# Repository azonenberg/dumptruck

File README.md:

# dumptruck
FPGA based dumper for flashes and more

## Main PCB errata

Bugs in the v0.1 PCB

* 1.0V shunt resistor is missing a zone fill. Will monitor droop under load and see if we need to add top layer power path.
* U33 is way too close to J10. Seems to have fit OK, not touching for now, but tough to assemble.
* INIT_B and PROG_B on FPGA are 1.8V signals but we try to drive with 3.3 from supervisor! Rework: add pull to 1.8V on board, open drain in super firmware
* JTAG connector VCC is connected to 3.3V. We need to supply 1.8 here. Temporary workaround: six pin extension cable, pass through JTAG + GND and supply 1.8V to dongle externally. Long term fix: interposer board
* DONE on FPGA is 1.8V signal driving 3.3V input on supervisor, too low for Vih. Rework: add 1.8V gate drive NMOS to pull low when done, invert logic in firmware

TODO: add HF caps to VCAP on STM32

## Breakout board errata

* v0.1 of parallel-nor-csp56 and dip8-qspi had EEPROM at 0xa0 which conflicted with MAC address EEPROM. Future breakouts use 0xa2 to avoid conflict

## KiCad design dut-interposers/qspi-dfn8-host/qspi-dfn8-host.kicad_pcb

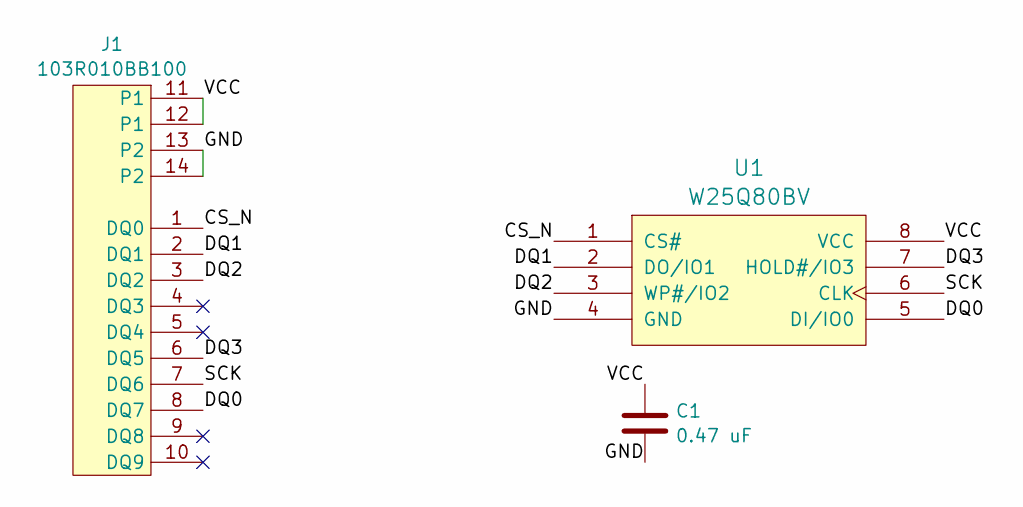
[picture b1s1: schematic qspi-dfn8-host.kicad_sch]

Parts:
C1: 0.47 uF; EIA_0402_CAP_NOSILK
J1: 103R010BB100; CONN_AMPHENOL_103R010BB100
U1: W25Q80BV; DFN_8_0.5MM_2x3MM_TALL

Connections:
/CS_N: J1.1 (DQ0), U1.1 (CS#)
/DQ0: J1.8 (DQ7), U1.5 (DI/IO0)
/DQ1: J1.2 (DQ1), U1.2 (DO/IO1)
/DQ2: J1.3 (DQ2), U1.3 (WP#/IO2)
/DQ3: J1.6 (DQ5), U1.7 (HOLD#/IO3)
/GND: C1.2, J1.13 (P2), J1.14 (P2), U1.4 (GND)
/SCK: J1.7 (DQ6), U1.6 (CLK)
/VCC: C1.1, J1.11 (P1), J1.12 (P1), U1.8 (VCC)

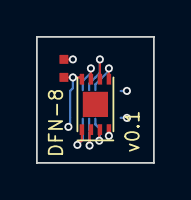
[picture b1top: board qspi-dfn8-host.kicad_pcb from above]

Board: 4 copper layers, 6.5 x 7.0 mm, 3 parts (1 on the bottom side), 8 nets.

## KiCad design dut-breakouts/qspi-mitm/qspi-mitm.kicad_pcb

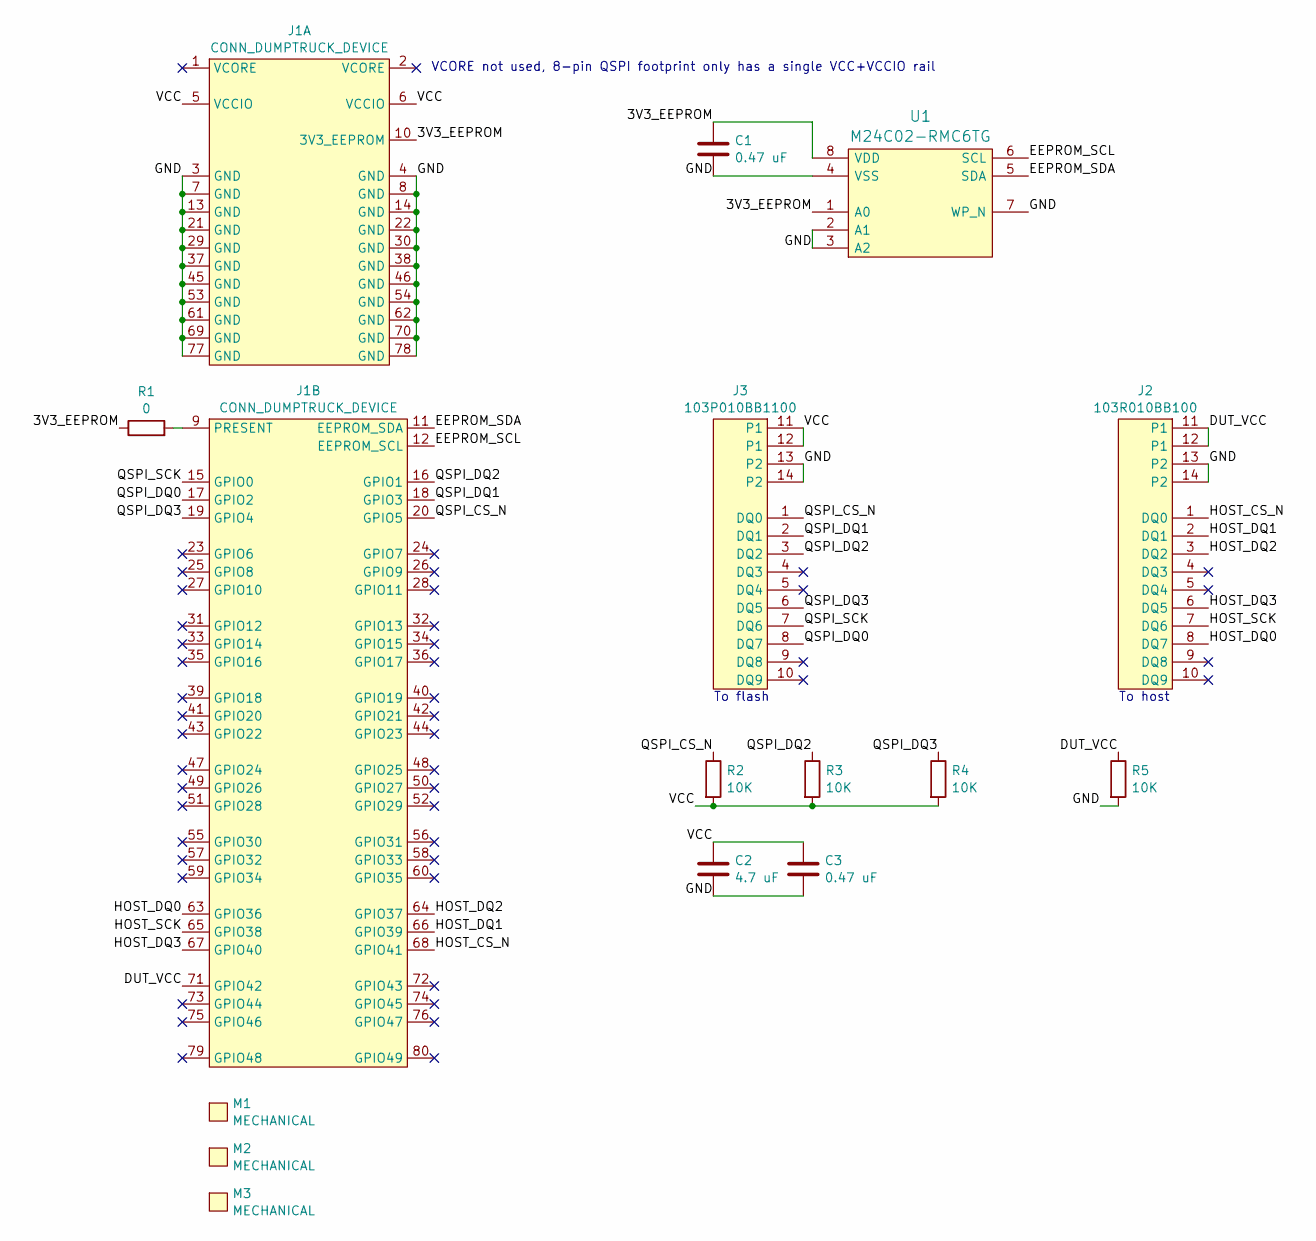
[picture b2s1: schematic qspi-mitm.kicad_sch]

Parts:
C1, C3: 0.47 uF; EIA_0402_CAP_NOSILK
C2: 4.7 uF; EIA_0603_CAP_NOSILK
J1: CONN_DUMPTRUCK_DEVICE; CONN_SAMTEC_BSE-040-01-L-D-A-TR
J2: 103R010BB100; CONN_AMPHENOL_103R010BB100
J3: 103P010BB1100; CONN_AMPHENOL_103P010BB100
M1: MECHANICAL; Logo_silk_ROHS_5x2.8mm
M2: MECHANICAL; Logo_silk_OSHW_6x6mm
M3: MECHANICAL; Logo_silk_WEEE_3.4x5mm
R1: 0; EIA_0402_RES_NOSILK
R2, R3, R4, R5: 10K; EIA_0402_RES_NOSILK
U1: M24C02-RMC6TG; DFN_8_0.5MM_2x3MM_TALL

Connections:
/3V3_EEPROM: C1.1, J1.10 (3V3_EEPROM), R1.1, U1.1 (A0), U1.8 (VDD)
/DUT_VCC: J1.71 (GPIO42), J2.11 (P1), J2.12 (P1), R5.1
/EEPROM_SCL: J1.12 (EEPROM_SCL), U1.6 (SCL)
/EEPROM_SDA: J1.11 (EEPROM_SDA), U1.5 (SDA)
/GND: C1.2, C2.2, C3.2, J1.3 (GND), J1.4 (GND), J1.7 (GND), J1.8 (GND), J1.13 (GND), J1.14 (GND), J1.21 (GND), J1.22 (GND), J1.29 (GND), J1.30 (GND), J1.37 (GND), J1.38 (GND), J1.45 (GND), J1.46 (GND), J1.53 (GND), J1.54 (GND), J1.61 (GND), J1.62 (GND), J1.69 (GND), J1.70 (GND), J1.77 (GND), J1.78 (GND), J2.13 (P2), J2.14 (P2), J3.13 (P2), J3.14 (P2), R5.2, U1.2 (A1), U1.3 (A2), U1.4 (VSS), U1.7 (WP_N)
/HOST_CS_N: J1.68 (GPIO41), J2.1 (DQ0)
/HOST_DQ0: J1.63 (GPIO36), J2.8 (DQ7)
/HOST_DQ1: J1.66 (GPIO39), J2.2 (DQ1)
/HOST_DQ2: J1.64 (GPIO37), J2.3 (DQ2)
/HOST_DQ3: J1.67 (GPIO40), J2.6 (DQ5)
/HOST_SCK: J1.65 (GPIO38), J2.7 (DQ6)
/QSPI_CS_N: J1.20 (GPIO5), J3.1 (DQ0), R2.1
/QSPI_DQ0: J1.17 (GPIO2), J3.8 (DQ7)
/QSPI_DQ1: J1.18 (GPIO3), J3.2 (DQ1)
/QSPI_DQ2: J1.16 (GPIO1), J3.3 (DQ2), R3.1
/QSPI_DQ3: J1.19 (GPIO4), J3.6 (DQ5), R4.1
/QSPI_SCK: J1.15 (GPIO0), J3.7 (DQ6)
/VCC: C2.1, C3.1, J1.5 (VCCIO), J1.6 (VCCIO), J3.11 (P1), J3.12 (P1), R2.2, R3.2, R4.2
unnamed: J1.9 (PRESENT), R1.2

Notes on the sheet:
To host
VCORE not used, 8-pin QSPI footprint only has a single VCC+VCCIO rail
To flash

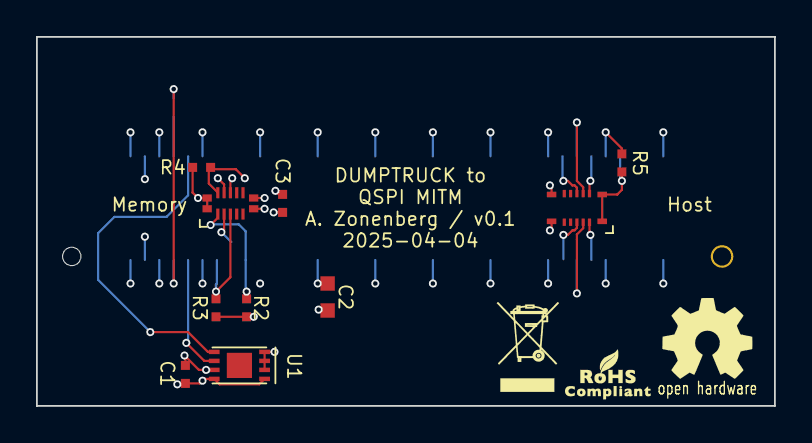
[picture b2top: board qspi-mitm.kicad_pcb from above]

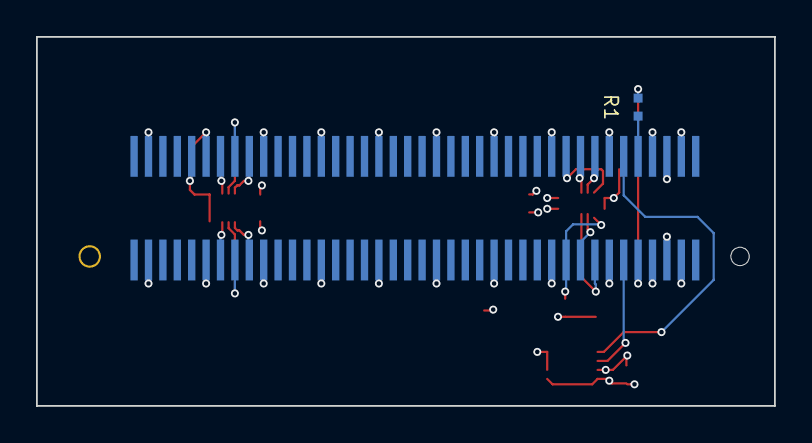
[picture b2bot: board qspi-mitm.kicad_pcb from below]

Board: 4 copper layers, 41.0 x 20.5 mm, 15 parts (2 on the bottom side), 19 nets.

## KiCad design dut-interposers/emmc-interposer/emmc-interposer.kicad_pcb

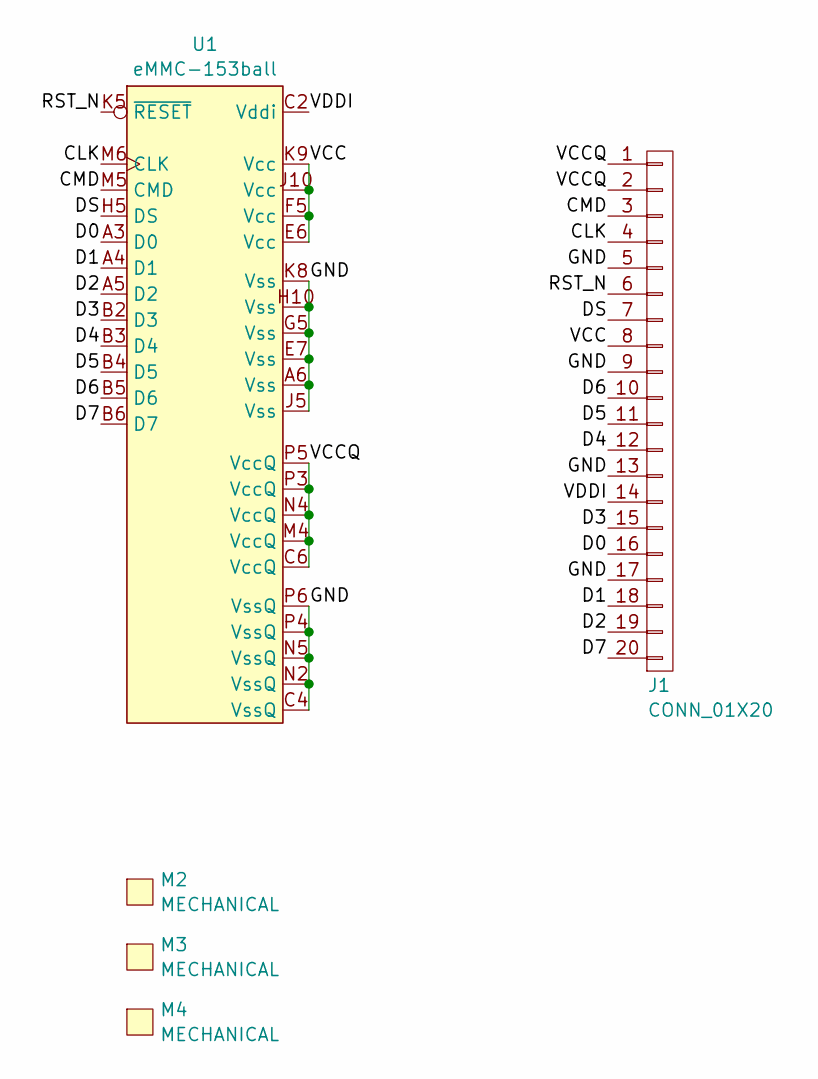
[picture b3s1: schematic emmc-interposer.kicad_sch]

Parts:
J1: CONN_01X20; CONN_FFC_0.5MM_3.5MM_1x20_2MM
M2: MECHANICAL; Logo_silk_OSHW_6x6mm
M3: MECHANICAL; Logo_silk_WEEE_3.4x5mm
M4: MECHANICAL; Logo_silk_ROHS_5x2.8mm
U1: eMMC-153ball; BGA_153_14x14_EMMC_BA_0.5MM_NCDEPOP_REVERSE

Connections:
/CLK: J1.4, U1.M6 (CLK)
/CMD: J1.3, U1.M5 (CMD)
/D0: J1.16, U1.A3 (D0)
/D1: J1.18, U1.A4 (D1)
/D2: J1.19, U1.A5 (D2)
/D3: J1.15, U1.B2 (D3)
/D4: J1.12, U1.B3 (D4)
/D5: J1.11, U1.B4 (D5)
/D6: J1.10, U1.B5 (D6)
/D7: J1.20, U1.B6 (D7)
/DS: J1.7, U1.H5 (DS)
/GND: J1.5, J1.9, J1.13, J1.17, U1.A6 (Vss), U1.C4 (VssQ), U1.E7 (Vss), U1.G5 (Vss), U1.H10 (Vss), U1.J5 (Vss), U1.K8 (Vss), U1.N2 (VssQ), U1.N5 (VssQ), U1.P4 (VssQ), U1.P6 (VssQ)
/RST_N: J1.6, U1.K5 (~RESET)
/VCC: J1.8, U1.E6 (Vcc), U1.F5 (Vcc), U1.J10 (Vcc), U1.K9 (Vcc)
/VCCQ: J1.1, J1.2, U1.C6 (VccQ), U1.M4 (VccQ), U1.N4 (VccQ), U1.P3 (VccQ), U1.P5 (VccQ)
/VDDI: J1.14, U1.C2 (Vddi)

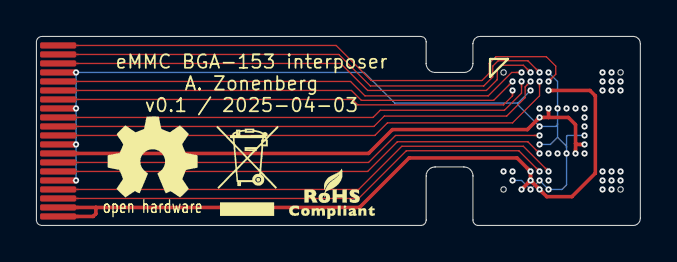
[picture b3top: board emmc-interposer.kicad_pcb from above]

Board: 2 copper layers, 33.5 x 10.5 mm, 5 parts (0 on the bottom side), 16 nets.

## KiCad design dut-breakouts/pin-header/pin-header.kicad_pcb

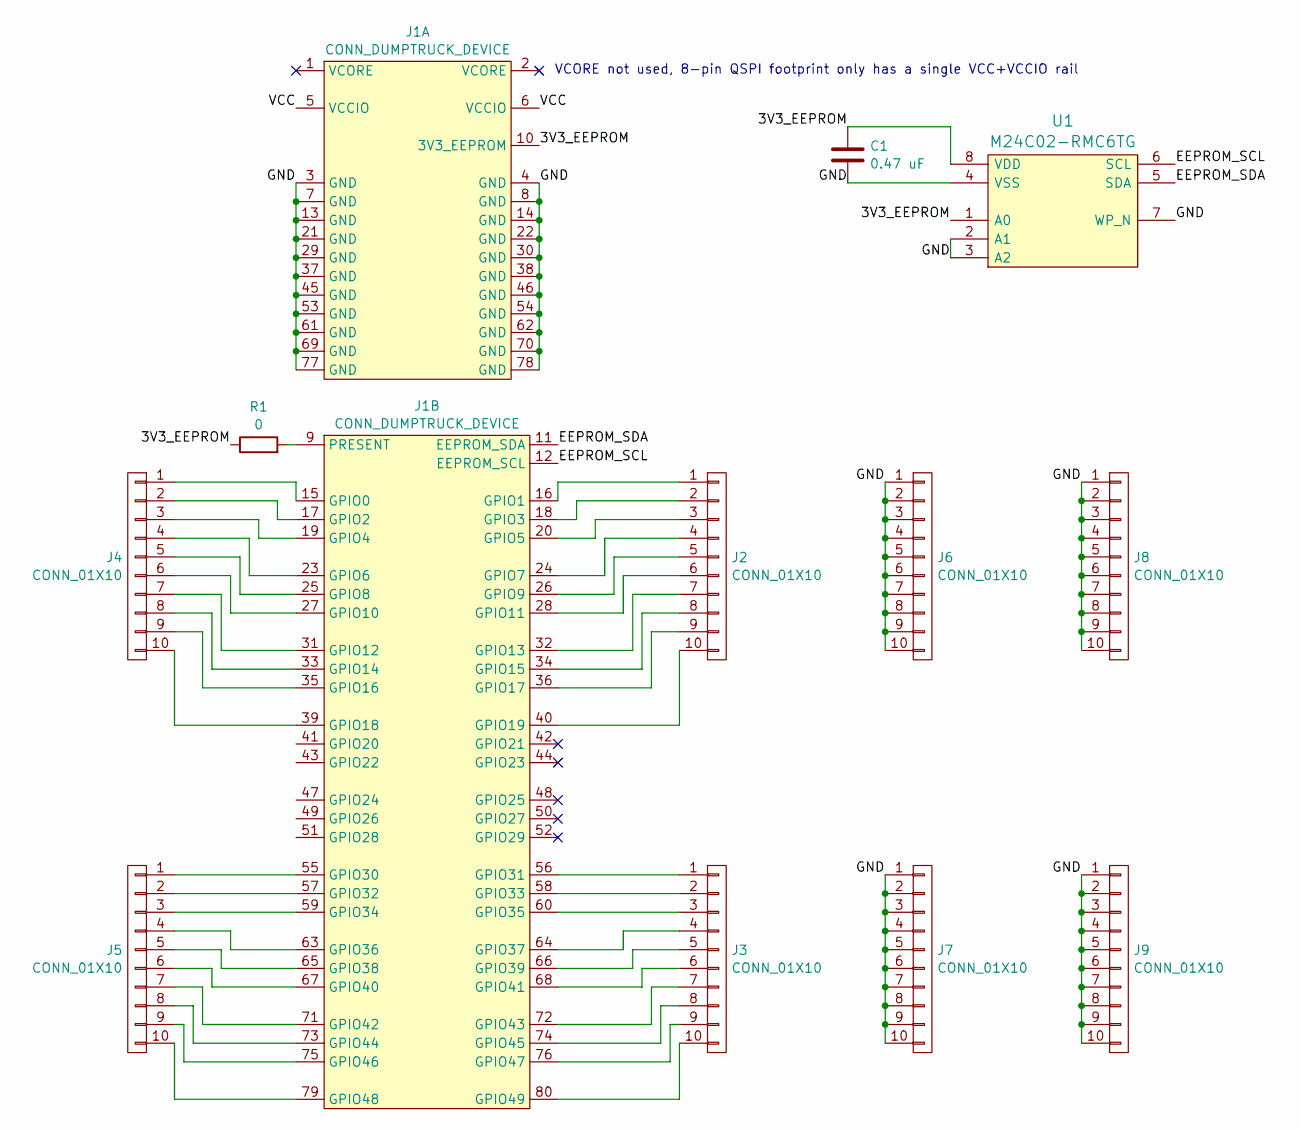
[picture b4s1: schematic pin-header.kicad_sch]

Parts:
C1: 0.47 uF; EIA_0402_CAP_NOSILK
J1: CONN_DUMPTRUCK_DEVICE; CONN_SAMTEC_BSE-040-01-L-D-A-TR
J2, J3, J4, J5, J6, J7, J8, J9: CONN_01X10; CONN_HEADER_2.54MM_1x10_REFLOW_NOSILK
R1: 0; EIA_0402_RES_NOSILK
U1: M24C02-RMC6TG; DFN_8_0.5MM_2x3MM_TALL

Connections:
/3V3_EEPROM: C1.1, J1.10 (3V3_EEPROM), R1.1, U1.1 (A0), U1.8 (VDD)
/EEPROM_SCL: J1.12 (EEPROM_SCL), U1.6 (SCL)
/EEPROM_SDA: J1.11 (EEPROM_SDA), U1.5 (SDA)
/GND: C1.2, J1.3 (GND), J1.4 (GND), J1.7 (GND), J1.8 (GND), J1.13 (GND), J1.14 (GND), J1.21 (GND), J1.22 (GND), J1.29 (GND), J1.30 (GND), J1.37 (GND), J1.38 (GND), J1.45 (GND), J1.46 (GND), J1.53 (GND), J1.54 (GND), J1.61 (GND), J1.62 (GND), J1.69 (GND), J1.70 (GND), J1.77 (GND), J1.78 (GND), J6.1, J6.2, J6.3, J6.4, J6.5, J6.6, J6.7, J6.8, J6.9, J6.10, J7.1, J7.2, J7.3, J7.4, J7.5, J7.6, J7.7, J7.8, J7.9, J7.10, J8.1, J8.2, J8.3, J8.4, J8.5, J8.6, J8.7, J8.8, J8.9, J8.10, J9.1, J9.2, J9.3, J9.4, J9.5, J9.6, J9.7, J9.8, J9.9, J9.10, U1.2 (A1), U1.3 (A2), U1.4 (VSS), U1.7 (WP_N)
/VCC: J1.5 (VCCIO), J1.6 (VCCIO)
unnamed: J1.15 (GPIO0), J4.1
unnamed: J1.16 (GPIO1), J2.1
unnamed: J1.17 (GPIO2), J4.2
unnamed: J1.18 (GPIO3), J2.2
unnamed: J1.19 (GPIO4), J4.3
unnamed: J1.20 (GPIO5), J2.3
unnamed: J1.23 (GPIO6), J4.4
unnamed: J1.24 (GPIO7), J2.4
unnamed: J1.25 (GPIO8), J4.5
unnamed: J1.26 (GPIO9), J2.5
unnamed: J1.27 (GPIO10), J4.6
unnamed: J1.28 (GPIO11), J2.6
unnamed: J1.31 (GPIO12), J4.7
unnamed: J1.32 (GPIO13), J2.7
unnamed: J1.33 (GPIO14), J4.8
unnamed: J1.34 (GPIO15), J2.8
unnamed: J1.35 (GPIO16), J4.9
unnamed: J1.36 (GPIO17), J2.9
unnamed: J1.39 (GPIO18), J4.10
unnamed: J1.40 (GPIO19), J2.10
unnamed: J1.55 (GPIO30), J5.1
unnamed: J1.56 (GPIO31), J3.1
unnamed: J1.57 (GPIO32), J5.2
unnamed: J1.58 (GPIO33), J3.2
unnamed: J1.59 (GPIO34), J5.3
unnamed: J1.60 (GPIO35), J3.3
unnamed: J1.63 (GPIO36), J5.4
unnamed: J1.64 (GPIO37), J3.4
unnamed: J1.65 (GPIO38), J5.5
unnamed: J1.66 (GPIO39), J3.5
unnamed: J1.67 (GPIO40), J5.6
unnamed: J1.68 (GPIO41), J3.6
unnamed: J1.71 (GPIO42), J5.7
unnamed: J1.72 (GPIO43), J3.7
unnamed: J1.73 (GPIO44), J5.8
unnamed: J1.74 (GPIO45), J3.8
unnamed: J1.75 (GPIO46), J5.9
unnamed: J1.76 (GPIO47), J3.9
unnamed: J1.79 (GPIO48), J5.10
unnamed: J1.80 (GPIO49), J3.10
unnamed: J1.9 (PRESENT), R1.2

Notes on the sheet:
VCORE not used, 8-pin QSPI footprint only has a single VCC+VCCIO rail

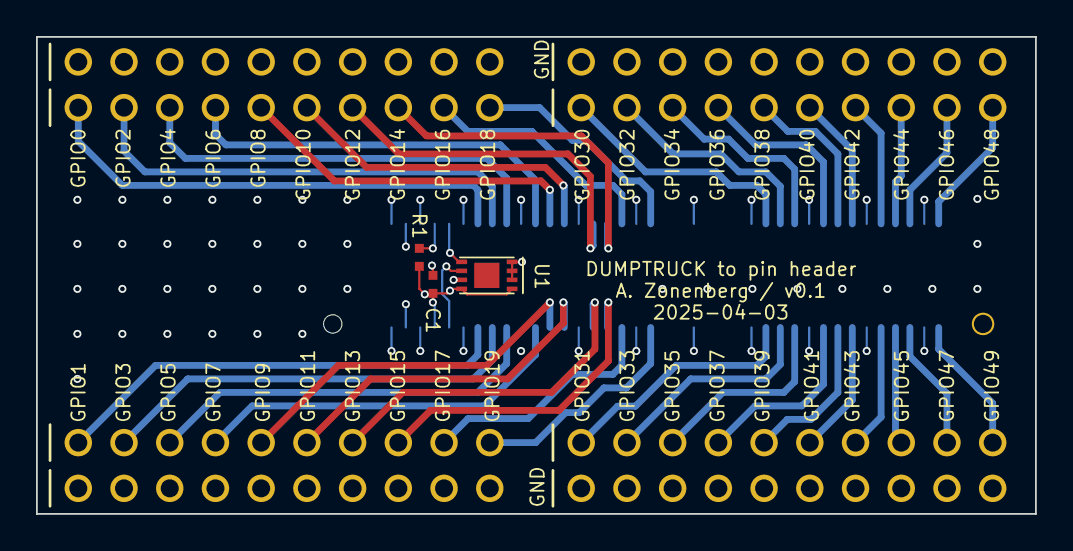
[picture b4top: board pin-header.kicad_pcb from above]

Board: 4 copper layers, 55.5 x 26.5 mm, 12 parts (1 on the bottom side), 46 nets.

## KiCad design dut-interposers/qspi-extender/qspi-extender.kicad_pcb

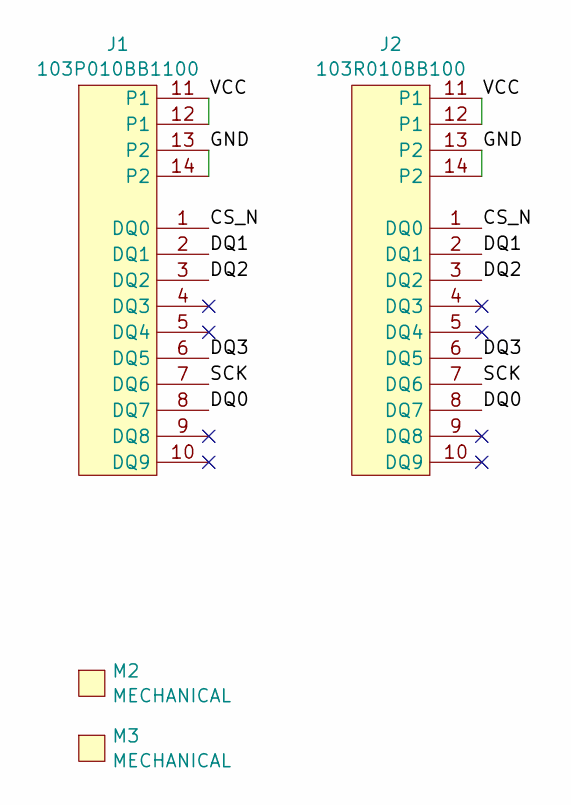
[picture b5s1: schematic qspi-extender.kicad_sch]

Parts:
J1: 103P010BB1100; CONN_AMPHENOL_103P010BB100
J2: 103R010BB100; CONN_AMPHENOL_103R010BB100
M2: MECHANICAL; Logo_silk_ROHS_5x2.8mm
M3: MECHANICAL; Logo_silk_OSHW_6x6mm

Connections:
/CS_N: J1.1 (DQ0), J2.1 (DQ0)
/DQ0: J1.8 (DQ7), J2.8 (DQ7)
/DQ1: J1.2 (DQ1), J2.2 (DQ1)
/DQ2: J1.3 (DQ2), J2.3 (DQ2)
/DQ3: J1.6 (DQ5), J2.6 (DQ5)
/GND: J1.13 (P2), J1.14 (P2), J2.13 (P2), J2.14 (P2)
/SCK: J1.7 (DQ6), J2.7 (DQ6)
/VCC: J1.11 (P1), J1.12 (P1), J2.11 (P1), J2.12 (P1)

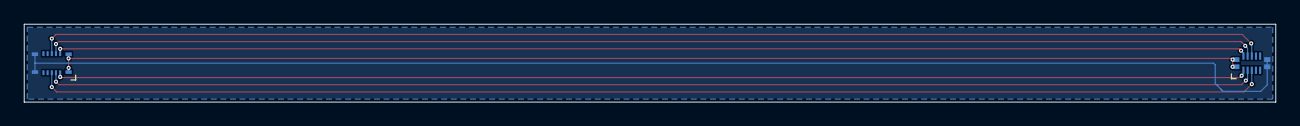
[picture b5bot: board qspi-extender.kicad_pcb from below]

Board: 2 copper layers, 104.5 x 6.5 mm, 4 parts (2 on the bottom side), 8 nets.

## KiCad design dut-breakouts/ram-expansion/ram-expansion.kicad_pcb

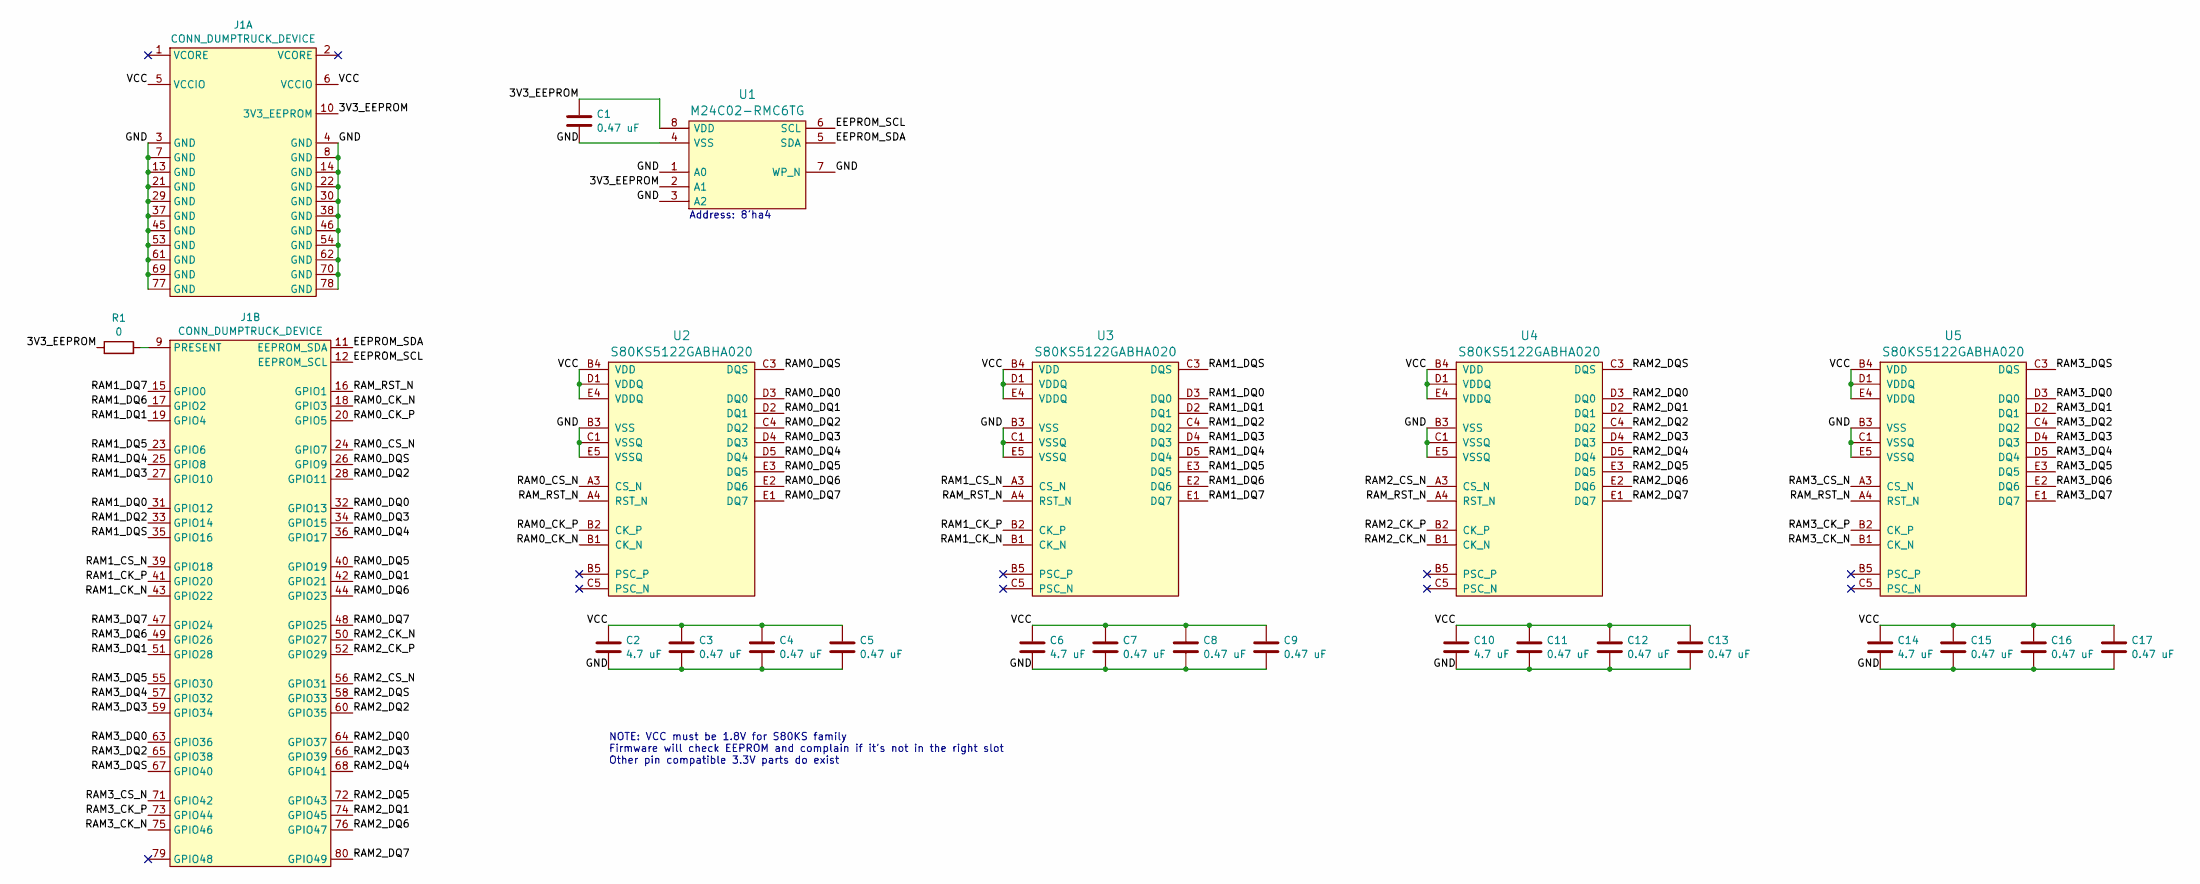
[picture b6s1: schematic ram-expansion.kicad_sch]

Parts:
C1, C3, C4, C5, C7, C8, C9, C11, C12, C13, C15, C16, C17: 0.47 uF; EIA_0402_CAP_NOSILK
C2, C6, C10, C14: 4.7 uF; EIA_0603_CAP_NOSILK
J1: CONN_DUMPTRUCK_DEVICE; CONN_SAMTEC_BSE-040-01-L-D-A-TR
R1: 0; EIA_0402_RES_NOSILK
U1: M24C02-RMC6TG; DFN_8_0.5MM_2x3MM_TALL
U2, U3, U4, U5: S80KS5122GABHA020; BGA_24_6x8_DEPOP1_1MM

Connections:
/3V3_EEPROM: C1.1, J1.10 (3V3_EEPROM), R1.1, U1.2 (A1), U1.8 (VDD)
/EEPROM_SCL: J1.12 (EEPROM_SCL), U1.6 (SCL)
/EEPROM_SDA: J1.11 (EEPROM_SDA), U1.5 (SDA)
/GND: C1.2, C2.2, C3.2, C4.2, C5.2, C6.2, C7.2, C8.2, C9.2, C10.2, C11.2, C12.2, C13.2, C14.2, C15.2, C16.2, C17.2, J1.3 (GND), J1.4 (GND), J1.7 (GND), J1.8 (GND), J1.13 (GND), J1.14 (GND), J1.21 (GND), J1.22 (GND), J1.29 (GND), J1.30 (GND), J1.37 (GND), J1.38 (GND), J1.45 (GND), J1.46 (GND), J1.53 (GND), J1.54 (GND), J1.61 (GND), J1.62 (GND), J1.69 (GND), J1.70 (GND), J1.77 (GND), J1.78 (GND), U1.1 (A0), U1.3 (A2), U1.4 (VSS), U1.7 (WP_N), U2.B3 (VSS), U2.C1 (VSSQ), U2.E5 (VSSQ), U3.B3 (VSS), U3.C1 (VSSQ), U3.E5 (VSSQ), U4.B3 (VSS), U4.C1 (VSSQ), U4.E5 (VSSQ), U5.B3 (VSS), U5.C1 (VSSQ), U5.E5 (VSSQ)
/RAM0_CK_N: J1.18 (GPIO3), U2.B1 (CK_N)
/RAM0_CK_P: J1.20 (GPIO5), U2.B2 (CK_P)
/RAM0_CS_N: J1.24 (GPIO7), U2.A3 (CS_N)
/RAM0_DQ0: J1.32 (GPIO13), U2.D3 (DQ0)
/RAM0_DQ1: J1.42 (GPIO21), U2.D2 (DQ1)
/RAM0_DQ2: J1.28 (GPIO11), U2.C4 (DQ2)
/RAM0_DQ3: J1.34 (GPIO15), U2.D4 (DQ3)
/RAM0_DQ4: J1.36 (GPIO17), U2.D5 (DQ4)
/RAM0_DQ5: J1.40 (GPIO19), U2.E3 (DQ5)
/RAM0_DQ6: J1.44 (GPIO23), U2.E2 (DQ6)
/RAM0_DQ7: J1.48 (GPIO25), U2.E1 (DQ7)
/RAM0_DQS: J1.26 (GPIO9), U2.C3 (DQS)
/RAM1_CK_N: J1.43 (GPIO22), U3.B1 (CK_N)
/RAM1_CK_P: J1.41 (GPIO20), U3.B2 (CK_P)
/RAM1_CS_N: J1.39 (GPIO18), U3.A3 (CS_N)
/RAM1_DQ0: J1.31 (GPIO12), U3.D3 (DQ0)
/RAM1_DQ1: J1.19 (GPIO4), U3.D2 (DQ1)
/RAM1_DQ2: J1.33 (GPIO14), U3.C4 (DQ2)
/RAM1_DQ3: J1.27 (GPIO10), U3.D4 (DQ3)
/RAM1_DQ4: J1.25 (GPIO8), U3.D5 (DQ4)
/RAM1_DQ5: J1.23 (GPIO6), U3.E3 (DQ5)
/RAM1_DQ6: J1.17 (GPIO2), U3.E2 (DQ6)
/RAM1_DQ7: J1.15 (GPIO0), U3.E1 (DQ7)
/RAM1_DQS: J1.35 (GPIO16), U3.C3 (DQS)
/RAM2_CK_N: J1.50 (GPIO27), U4.B1 (CK_N)
/RAM2_CK_P: J1.52 (GPIO29), U4.B2 (CK_P)
/RAM2_CS_N: J1.56 (GPIO31), U4.A3 (CS_N)
/RAM2_DQ0: J1.64 (GPIO37), U4.D3 (DQ0)
/RAM2_DQ1: J1.74 (GPIO45), U4.D2 (DQ1)
/RAM2_DQ2: J1.60 (GPIO35), U4.C4 (DQ2)
/RAM2_DQ3: J1.66 (GPIO39), U4.D4 (DQ3)
/RAM2_DQ4: J1.68 (GPIO41), U4.D5 (DQ4)
/RAM2_DQ5: J1.72 (GPIO43), U4.E3 (DQ5)
/RAM2_DQ6: J1.76 (GPIO47), U4.E2 (DQ6)
/RAM2_DQ7: J1.80 (GPIO49), U4.E1 (DQ7)
/RAM2_DQS: J1.58 (GPIO33), U4.C3 (DQS)
/RAM3_CK_N: J1.75 (GPIO46), U5.B1 (CK_N)
/RAM3_CK_P: J1.73 (GPIO44), U5.B2 (CK_P)
/RAM3_CS_N: J1.71 (GPIO42), U5.A3 (CS_N)
/RAM3_DQ0: J1.63 (GPIO36), U5.D3 (DQ0)
/RAM3_DQ1: J1.51 (GPIO28), U5.D2 (DQ1)
/RAM3_DQ2: J1.65 (GPIO38), U5.C4 (DQ2)
/RAM3_DQ3: J1.59 (GPIO34), U5.D4 (DQ3)
/RAM3_DQ4: J1.57 (GPIO32), U5.D5 (DQ4)
/RAM3_DQ5: J1.55 (GPIO30), U5.E3 (DQ5)
/RAM3_DQ6: J1.49 (GPIO26), U5.E2 (DQ6)
/RAM3_DQ7: J1.47 (GPIO24), U5.E1 (DQ7)
/RAM3_DQS: J1.67 (GPIO40), U5.C3 (DQS)
/RAM_RST_N: J1.16 (GPIO1), U2.A4 (RST_N), U3.A4 (RST_N), U4.A4 (RST_N), U5.A4 (RST_N)
/VCC: C2.1, C3.1, C4.1, C5.1, C6.1, C7.1, C8.1, C9.1, C10.1, C11.1, C12.1, C13.1, C14.1, C15.1, C16.1, C17.1, J1.5 (VCCIO), J1.6 (VCCIO), U2.B4 (VDD), U2.D1 (VDDQ), U2.E4 (VDDQ), U3.B4 (VDD), U3.D1 (VDDQ), U3.E4 (VDDQ), U4.B4 (VDD), U4.D1 (VDDQ), U4.E4 (VDDQ), U5.B4 (VDD), U5.D1 (VDDQ), U5.E4 (VDDQ)
unnamed: J1.9 (PRESENT), R1.2

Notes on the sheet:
Address: 8'ha4
NOTE: VCC must be 1.8V for S80KS family Firmware will check EEPROM and complain if it's not in the right slot Other pin compatible 3.3V parts do exist

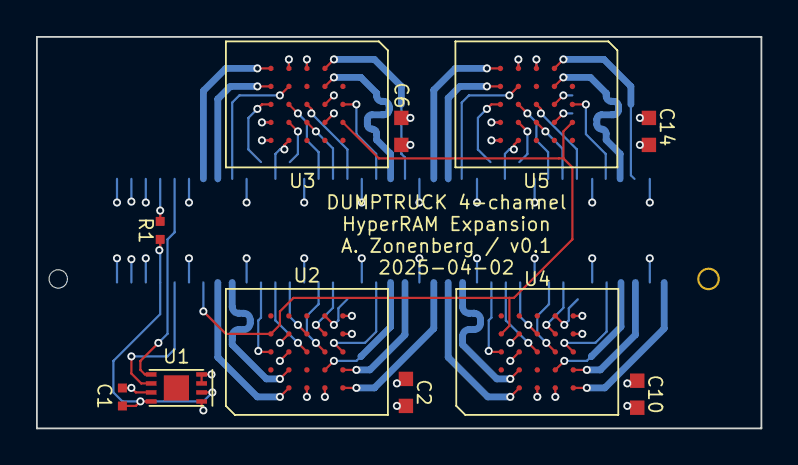
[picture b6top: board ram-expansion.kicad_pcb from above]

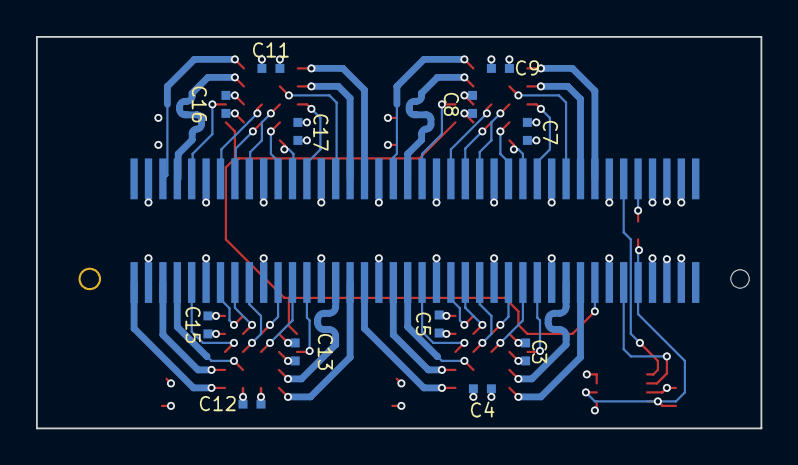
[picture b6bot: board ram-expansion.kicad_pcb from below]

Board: 4 copper layers, 40.2 x 21.8 mm, 24 parts (13 on the bottom side), 55 nets.

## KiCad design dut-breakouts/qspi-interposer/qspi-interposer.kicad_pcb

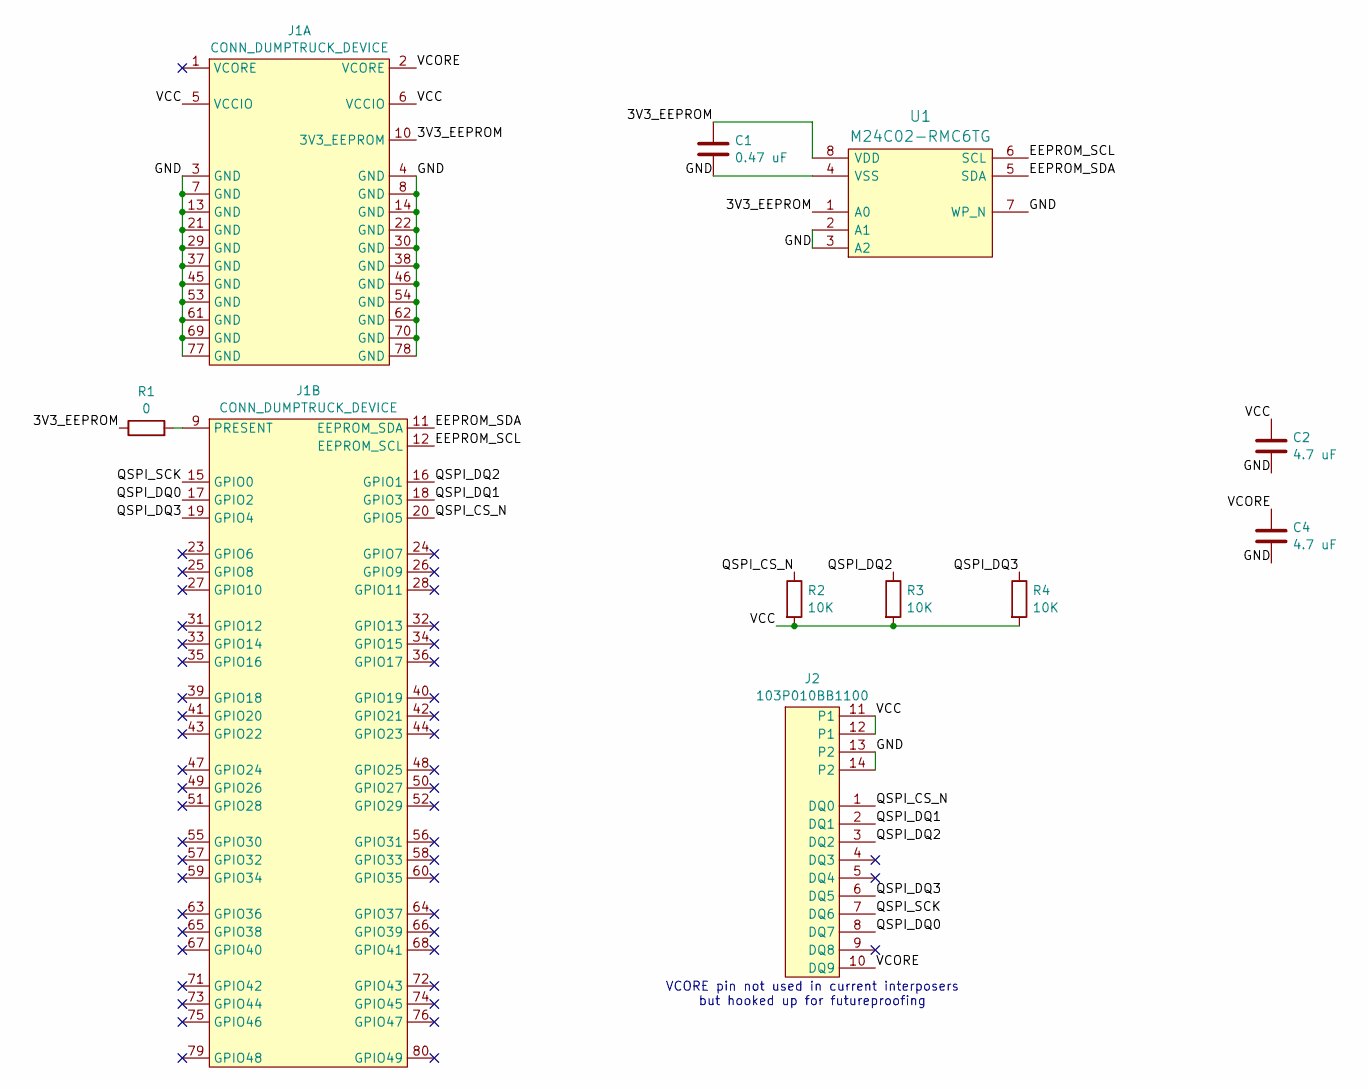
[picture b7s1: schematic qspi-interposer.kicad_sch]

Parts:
C1: 0.47 uF; EIA_0402_CAP_NOSILK
C2, C4: 4.7 uF; EIA_0603_CAP_NOSILK
J1: CONN_DUMPTRUCK_DEVICE; CONN_SAMTEC_BSE-040-01-L-D-A-TR
J2: 103P010BB1100; CONN_AMPHENOL_103P010BB100
R1: 0; EIA_0402_RES_NOSILK
R2, R3, R4: 10K; EIA_0402_RES_NOSILK
U1: M24C02-RMC6TG; DFN_8_0.5MM_2x3MM_TALL

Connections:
/3V3_EEPROM: C1.1, J1.10 (3V3_EEPROM), R1.1, U1.1 (A0), U1.8 (VDD)
/EEPROM_SCL: J1.12 (EEPROM_SCL), U1.6 (SCL)
/EEPROM_SDA: J1.11 (EEPROM_SDA), U1.5 (SDA)
/GND: C1.2, C2.2, C4.2, J1.3 (GND), J1.4 (GND), J1.7 (GND), J1.8 (GND), J1.13 (GND), J1.14 (GND), J1.21 (GND), J1.22 (GND), J1.29 (GND), J1.30 (GND), J1.37 (GND), J1.38 (GND), J1.45 (GND), J1.46 (GND), J1.53 (GND), J1.54 (GND), J1.61 (GND), J1.62 (GND), J1.69 (GND), J1.70 (GND), J1.77 (GND), J1.78 (GND), J2.13 (P2), J2.14 (P2), U1.2 (A1), U1.3 (A2), U1.4 (VSS), U1.7 (WP_N)
/QSPI_CS_N: J1.20 (GPIO5), J2.1 (DQ0), R2.1
/QSPI_DQ0: J1.17 (GPIO2), J2.8 (DQ7)
/QSPI_DQ1: J1.18 (GPIO3), J2.2 (DQ1)
/QSPI_DQ2: J1.16 (GPIO1), J2.3 (DQ2), R3.1
/QSPI_DQ3: J1.19 (GPIO4), J2.6 (DQ5), R4.1
/QSPI_SCK: J1.15 (GPIO0), J2.7 (DQ6)
/VCC: C2.1, J1.5 (VCCIO), J1.6 (VCCIO), J2.11 (P1), J2.12 (P1), R2.2, R3.2, R4.2
/VCORE: C4.1, J1.2 (VCORE), J2.10 (DQ9)
unnamed: J1.9 (PRESENT), R1.2

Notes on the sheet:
VCORE pin not used in current interposers but hooked up for futureproofing

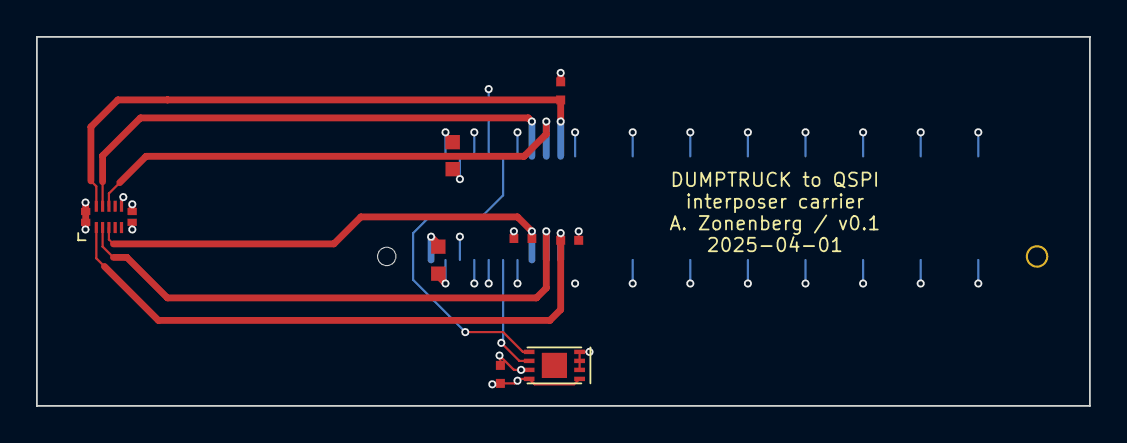
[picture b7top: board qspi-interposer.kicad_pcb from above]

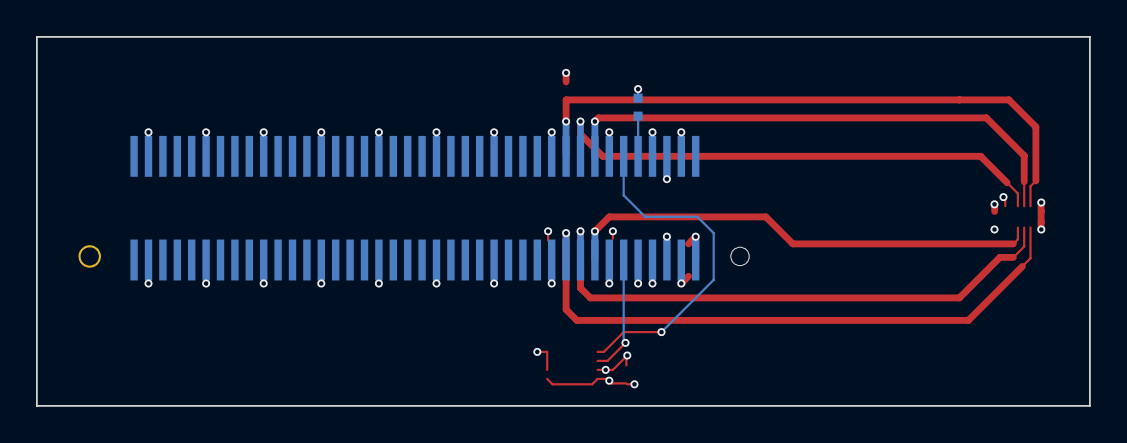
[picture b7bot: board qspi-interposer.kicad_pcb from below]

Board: 4 copper layers, 58.5 x 20.5 mm, 10 parts (2 on the bottom side), 13 nets.

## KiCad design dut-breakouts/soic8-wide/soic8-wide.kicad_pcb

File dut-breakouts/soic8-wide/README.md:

# soic8-wide

Breakout for wide (208 mil) SOIC-8

Designed for this socket https://www.aliexpress.us/item/3256807343973730.html

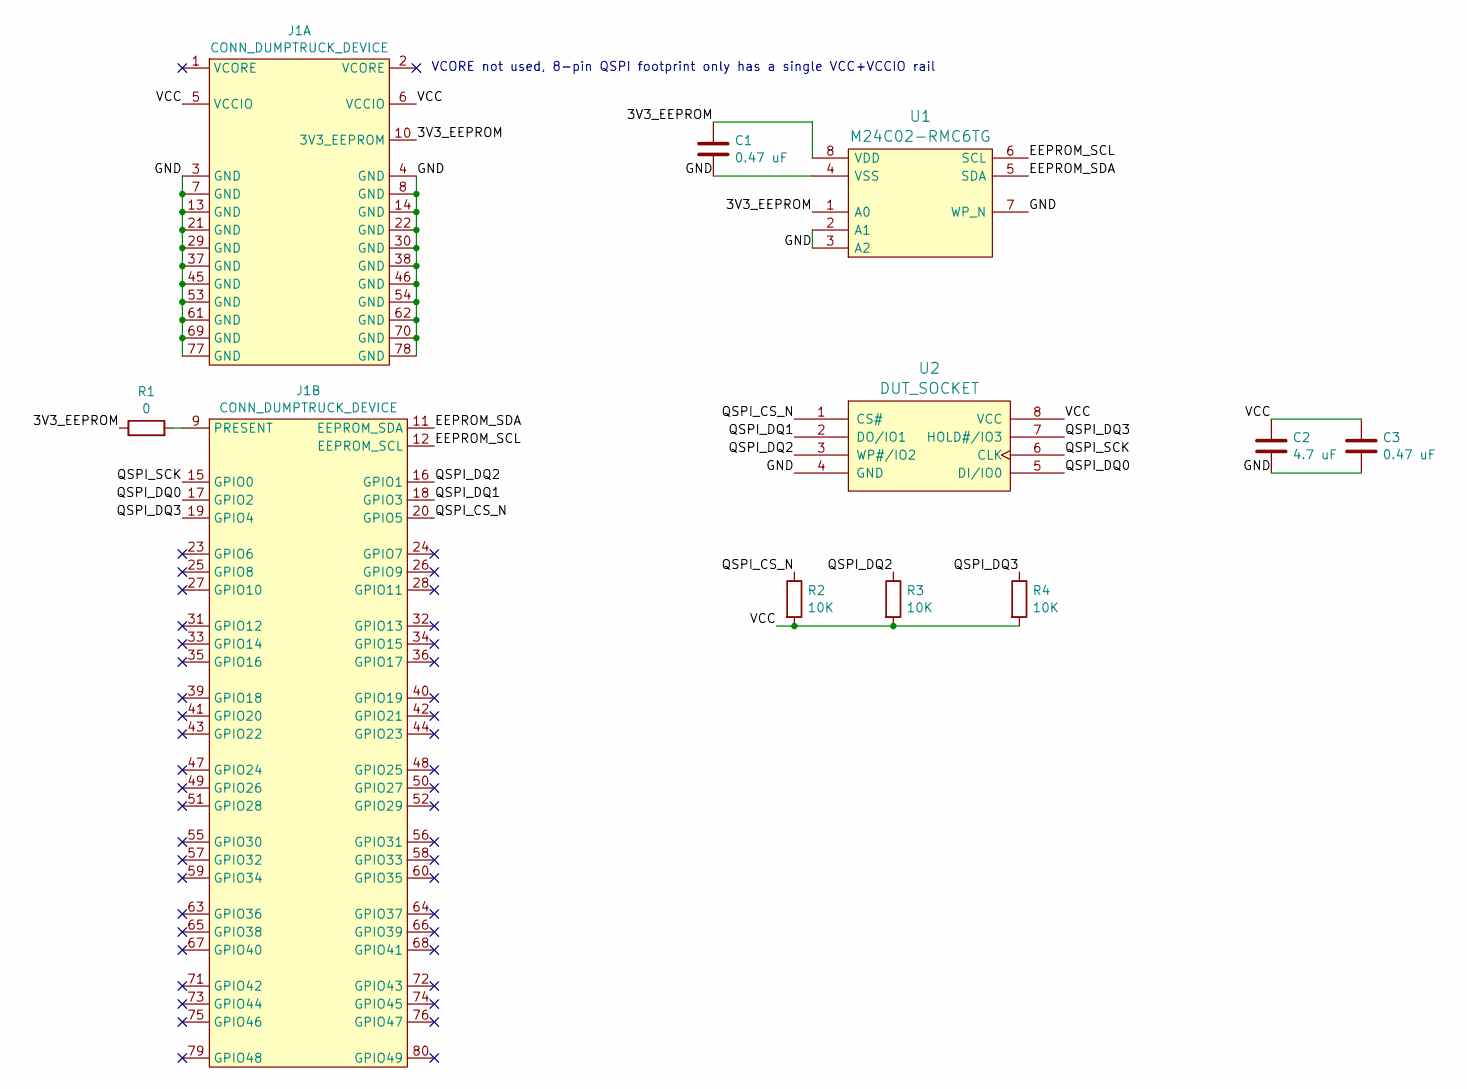
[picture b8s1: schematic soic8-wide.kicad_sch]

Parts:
C1, C3: 0.47 uF; EIA_0402_CAP_NOSILK
C2: 4.7 uF; EIA_0603_CAP_NOSILK
J1: CONN_DUMPTRUCK_DEVICE; CONN_SAMTEC_BSE-040-01-L-D-A-TR
R1: 0; EIA_0402_RES_NOSILK
R2, R3, R4: 10K; EIA_0402_RES_NOSILK
U1: M24C02-RMC6TG; DFN_8_0.5MM_2x3MM_TALL
U2: DUT_SOCKET; SOIC_8_5.3MM

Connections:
/3V3_EEPROM: C1.1, J1.10 (3V3_EEPROM), R1.1, U1.1 (A0), U1.8 (VDD)
/EEPROM_SCL: J1.12 (EEPROM_SCL), U1.6 (SCL)
/EEPROM_SDA: J1.11 (EEPROM_SDA), U1.5 (SDA)
/GND: C1.2, C2.2, C3.2, J1.3 (GND), J1.4 (GND), J1.7 (GND), J1.8 (GND), J1.13 (GND), J1.14 (GND), J1.21 (GND), J1.22 (GND), J1.29 (GND), J1.30 (GND), J1.37 (GND), J1.38 (GND), J1.45 (GND), J1.46 (GND), J1.53 (GND), J1.54 (GND), J1.61 (GND), J1.62 (GND), J1.69 (GND), J1.70 (GND), J1.77 (GND), J1.78 (GND), U1.2 (A1), U1.3 (A2), U1.4 (VSS), U1.7 (WP_N), U2.4 (GND)
/QSPI_CS_N: J1.20 (GPIO5), R2.1, U2.1 (CS#)
/QSPI_DQ0: J1.17 (GPIO2), U2.5 (DI/IO0)
/QSPI_DQ1: J1.18 (GPIO3), U2.2 (DO/IO1)
/QSPI_DQ2: J1.16 (GPIO1), R3.1, U2.3 (WP#/IO2)
/QSPI_DQ3: J1.19 (GPIO4), R4.1, U2.7 (HOLD#/IO3)
/QSPI_SCK: J1.15 (GPIO0), U2.6 (CLK)
/VCC: C2.1, C3.1, J1.5 (VCCIO), J1.6 (VCCIO), R2.2, R3.2, R4.2, U2.8 (VCC)
unnamed: J1.9 (PRESENT), R1.2

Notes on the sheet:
VCORE not used, 8-pin QSPI footprint only has a single VCC+VCCIO rail

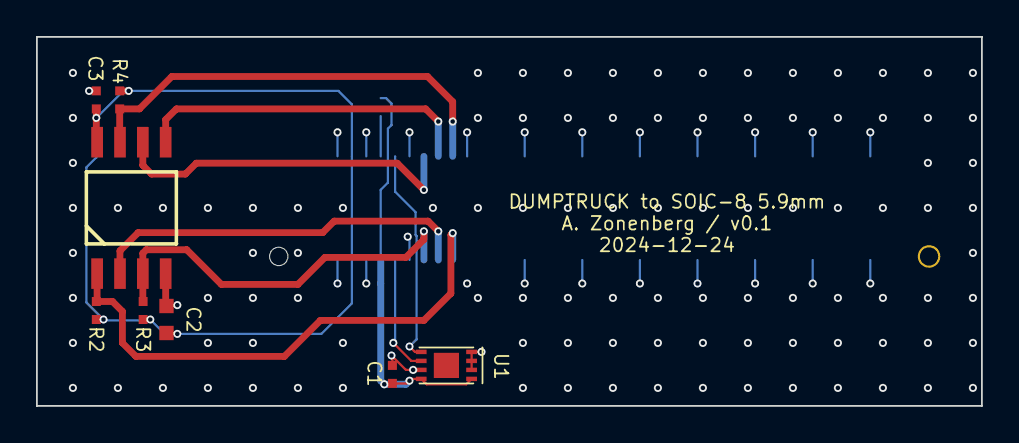
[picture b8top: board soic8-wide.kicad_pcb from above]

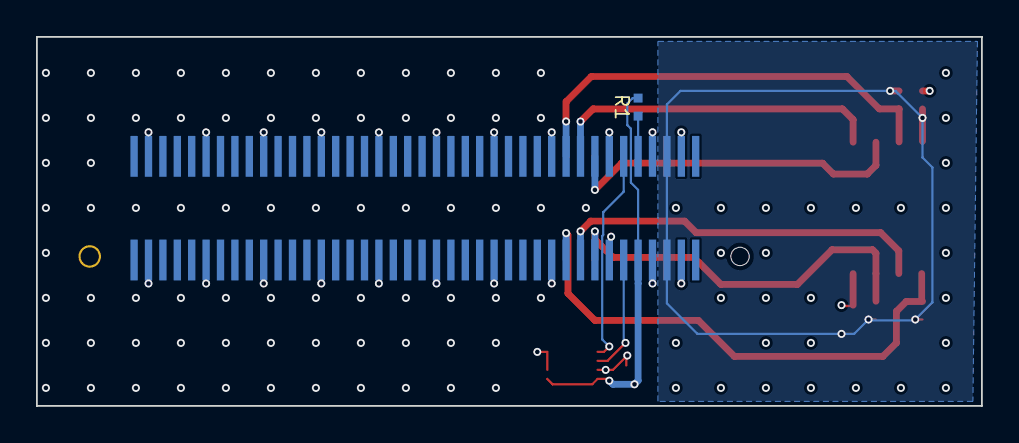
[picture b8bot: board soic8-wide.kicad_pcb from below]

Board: 4 copper layers, 52.5 x 20.5 mm, 10 parts (2 on the bottom side), 12 nets.
